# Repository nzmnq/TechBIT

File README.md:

# TechBIT Hardware (`scheme`) — Плата колісного вузла

Апаратна частина системи моніторингу вібрації, стану гальм/підшипників та температури коліс автомобіля **TechBIT**.  
Ця гілка (`scheme`) містить **лише апаратну частину (KiCad 10 PCB, 3D-моделі, генератори та файли для виготовлення)** — веб-додаток знаходиться у гілках `main` / `web-development`.

| Вигляд зверху (`F.Cu` — модулі та THT) | Вигляд знизу (`B.Cu` — SMD на міді) |
|---|---|
|  |  |

---

## Структура репозиторію

```text
.
├── kicad/                                      # Проєкт KiCad 10
│   ├── Wheel_Sensor_Amplifier.kicad_pro        # Файл проєкту KiCad 10
│   ├── Wheel_Sensor_Amplifier.kicad_sch        # Принципова схема та перелік зв'язків
│   ├── Wheel_Sensor_Amplifier.kicad_pcb        # Розводка плати (66 × 50 мм, 1 шар B.Cu)
│   └── Wheel_Sensor_Amplifier_Panel_A4.kicad_pcb  # Панель 3×5 (15 плат на аркуш A4)
├── 3dmodels/                                   # Локальні 3D-моделі модулів (.wrl)
├── renders/                                    # 3D-рендери та читабельна схема розмітки (.png)
├── print/                                      # Готові PDF 1:1 для ЛУТ, УФ-маски та монтажу
├── scripts/                                    # Python-скрипти генерації проєкту і макетів
│   ├── generate_project.py                     # Генератор KiCad-проєкту (single + 15x panel)
│   ├── make_plate_151x102.py                   # Генератор листів під текстоліт 151×102 мм
│   ├── make_a4_mixed_sheet.py                  # Генератор змішаного аркуша A4 (5 комплектів)
│   └── make_top_half_stencils.py               # Генератор УФ-маски на верхню половину A4
├── .gitignore
├── LICENSE
└── README.md
```

---

## Технічні характеристики плати (`Wheel Sensor Amplifier`)

- **Габарити однієї плати:** `66.0 × 50.0 мм` (оптимально для розміщення `2×2 = 4` плат на заготовці `151×102 мм` або `3×5 = 15` плат на A4).
- **Топологія:** **одностороння мідь (`B.Cu`)**, розведена без перемичок та без масивної заливки `GND` — розрахована під домашнє травлення (ЛУТ + лимонна кислота / перекис водню або хлорне залізо).
- **Гідроізоляція під заливку компаундом:** усі силові, шинні та сенсорні інтерфейси (`J1`, `J2`, `J3`) винесені кутовими роз'ємами по периметру для зручного заливання плати епоксидною смолою.
- **Паяльна маска:** розширення вікон `pad_to_mask_clearance = 0.15 мм`, суцільне заповнення контактних площадок на фотошаблонах (`B.Mask`).

---

## Склад компонентів (BOM)

### Верхня сторона (`F.Cu` — вивідні компоненти, модулі та роз'єми)
| Позиція | Компонент / Модуль | Номінал / Тип | Призначення |
|---|---|---|---|
| `U2` | Мікроконтролер | `ESP32-C3 SuperMini` | Оцифровка АЦП, I2C, CAN/TWAI (`USB-C` донизу) |
| `U1` | Операційний підсилювач | `MCP6002-I/P` (панелька `DIP-8`) | Зарядовий підсилювач ($K \approx 3$) + буфер |
| `MOD1` | DC-DC понижувач | `Mini360` (`12V → 5V`) | Живлення вузла від бортмережі авто |
| `MOD2` | CAN-трансивер | `SN65HVD230` (3.3V, 6-pin) | Інтерфейс CAN-шини (`CANH` / `CANL`) |
| `J1` | Клемник датчика вібрації | `15EDGR-5.08-02P` / `KF301-2P` (кутовий) | Вхід п'єзодатчика (`1=PIEZO+`, `2=GND`) |
| `J2` | Клемник живлення та CAN | `15EDGR-5.08-04P` / `KF301-4P` (кутовий) | Автомагістраль (`1=+12V`, `2=GND`, `3=CAN_L`, `4=CAN_H`) |
| `J3` | Роз'єм датчика температури | `JST-XH S4B-XH-A` (4-pin, кутовий 2.5 мм) | Вологостійкий датчик `GY-SHT40` (`1=3V3`, `2=GND`, `3=SDA`, `4=SCL`) |
| `R1` | Резистор THT 0.25W | `10 kΩ` | Обмеження вхідного струму ОП |
| `R2`, `R3` | Резистори THT 0.25W | `100 kΩ` (2 шт.) | Дільник опорної напруги `1.65 В` (`Vref`) |
| `R5` | Резистор THT 0.25W | `100 Ω` | Ізолюючий резистор перед ФНЧ та АЦП |
| `C5` | Конденсатор електролітичний | `10 µF` (радиальний D5/P2.5) | Фільтрація `Vref` (`+` до `VREF_1V65`) |

### Нижня сторона (`B.Cu` — SMD-монтаж на мідні доріжки)
| Позиція | Корпус | Номінал | Призначення |
|---|---|---|---|
| `D1` | `SOT-23` | `BAT54S` | Здвоєний діод Шотткі (захист входу від сплесків) |
| `C1` | `0805` | `1 nF` (NP0/C0G) | Вхідний розділовий конденсатор |
| `C2` | `0805` | `330 pF` (NP0/C0G, 50V) | Конденсатор зворотного зв'язку ($K = C_1/C_2 \approx 3$) |
| `R4` | `1206` | `4.7 MΩ` | Розрядний резистор зарядового інтегратора |
| `C3` | `1206` | `100 nF` | Блокування живлення `+3V3` біля `U1` |
| `C4` | `1206` | `100 nF` | ФНЧ антиаліасингу на вході АЦП (`R5 + C4`) |

---

## Розпіновка `ESP32-C3 SuperMini` (`U2`)

| Пін модуля | Сигнал (Net) | Підключення |
|---|---|---|
| Pin 16 (`5V`) | `+5V_BUCK` | Вихід `MOD1` (`Mini360`) |
| Pin 15 (`GND`) | `GND` | Загальна земля |
| Pin 14 (`3V3`) | `+3V3` | Живлення `U1`, `MOD2`, `J3`, `R2`, `D1` |
| Pin 11 | `ADC_SIGNAL` | Аналоговий вихід каскаду (`R5` / `C4`) |
| Pin 8 | `CAN_TX` | `MOD2` pin 3 |
| Pin 7 | `CAN_RX` | `MOD2` pin 4 |
| Pin 5 | `I2C_SCL` | `J3` pin 4 (`GY-SHT40 SCL`) |
| Pin 4 | `I2C_SDA` | `J3` pin 3 (`GY-SHT40 SDA`) |

---

## Свердління отворів

| Діаметр свердла | К-сть отворів (на 1 плату) | Елементи |
|---|---|---|
| **0.8 мм** | 40 | `R1, R2, R3, R5`, `C5`, панелька `U1` (`DIP-8`), гребінки `U2` і `MOD2` |
| **0.9 мм** | 4 | Боковий роз'єм `J3` (`JST-XH`) |
| **1.0 мм** | 4 | Контактні штирі `MOD1` (`Mini360`) |
| **1.3 мм** | 6 | Силові/шинні клемники `J1` і `J2` (`15EDGR-5.08` / `KF301`) |

---

## Файли для друку та виготовлення ([`print/`](print/))

> [!IMPORTANT]
> Друкуйте всі PDF **строго в масштабі `100%` / «Фактичний розмір»** (`Actual Size`). Вимикайте *Fit to Page* та *Borderless* (інакше драйвер розтягне плату на 2–3% і отвори не зійдуться). Перед перенесенням перевірте контрольні лінійки на аркуші (`150 мм` / `100 мм`).

| Файл | Призначення |
|---|---|
| `Plate_151x102_PagePro1350W_A4.pdf` | Оптимізовано під заготовку **`151×102 мм`** (4 плати `2×2`) та поля `≥ 4 мм`: мідь, дзеркальний верх, нижнє SMD-маркування, комбо-аркуш та УФ-маска |
| `SolderMask_UV_Film_Plate_151x102_A4.pdf` | Фотошаблони УФ паяльної маски під пластину `151×102 мм` (тонером вниз до міді + дзеркальний варіант) |
| `SolderMask_UV_Top_Half_A4.pdf` | УФ-маска, розміщена **тільки на верхній половині A4** (економія плівки: 2 плати, 4 плати `2×2`, або 2 пластини) |
| `A4_Mixed_Top_Bottom_Copper_5sets.pdf` | Змішаний аркуш A4: 5 повних комплектів (верх + мідь + низ SMD) + аркуш маркування |
| `Assembly_Guide_Readable_A4.pdf` | Читабельна карта монтажу та пайки (3 сторінки) |
| `LUT_Bottom_Copper_Max_Panel_15x_A4.pdf` / `_Single_A4.pdf` | Мідні доріжки `B.Cu` для ЛУТ (панель 15× або 1 плата) |
| `LUT_Top_Silkscreen_Transfer_Mirrored_15x_A4.pdf` / `_Single_A4.pdf` | Віддзеркалена верхня розмітка `F.SilkS` для переносу праскою |
| `LUT_Bottom_SMD_Markings_Single_A4.pdf` | Маркування SMD знизу (`B.SilkS`) |
| `SolderMask_UV_Film_15x_A4.pdf` / `_Single_A4.pdf` | Фотошаблони УФ-маски на панель 15× або 1 плату |

---

## Перегенерація та калібрування під принтер

Для повторної генерації файлів потрібні **Python 3**, **KiCad 10 (`kicad-cli`)**, **Google Chrome** (headless PDF) та `pypdf`:

```bash
# З кореня репозиторію:

# 1. Перегенерувати проєкт KiCad (одиночна плата, 15x панель, схема)
python3 scripts/generate_project.py

# 2. Перегенерувати аркуші для друку A4
python3 scripts/make_a4_mixed_sheet.py
python3 scripts/make_top_half_stencils.py

# 3. Перегенерувати аркуші під пластину 151x102 мм (з поправкою масштабу принтера у %)
python3 scripts/make_plate_151x102.py --sx 100.0 --sy 100.0
python3 scripts/make_plate_151x102.py --mask --sx 100.0 --sy 100.0
```

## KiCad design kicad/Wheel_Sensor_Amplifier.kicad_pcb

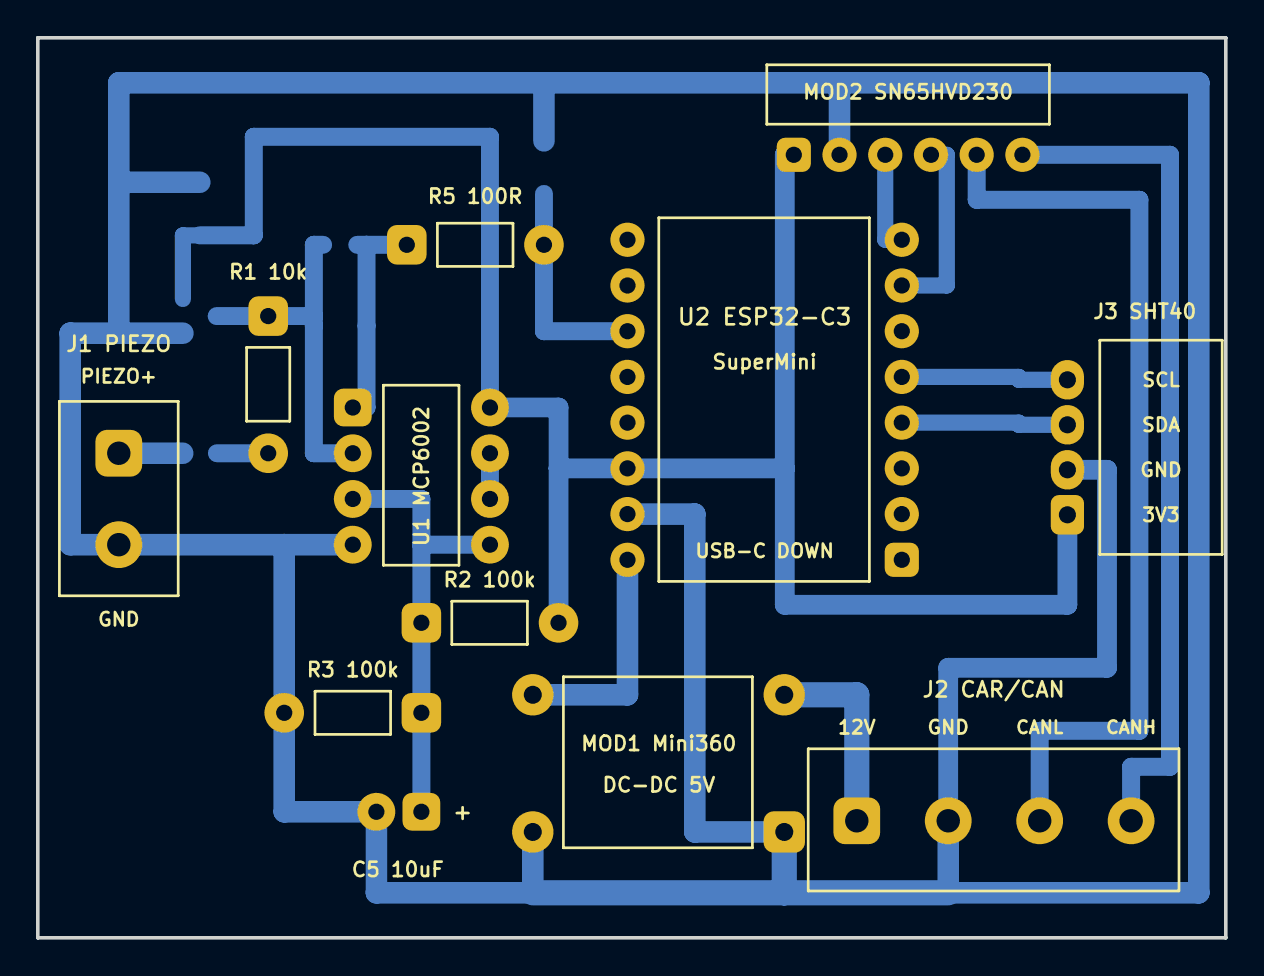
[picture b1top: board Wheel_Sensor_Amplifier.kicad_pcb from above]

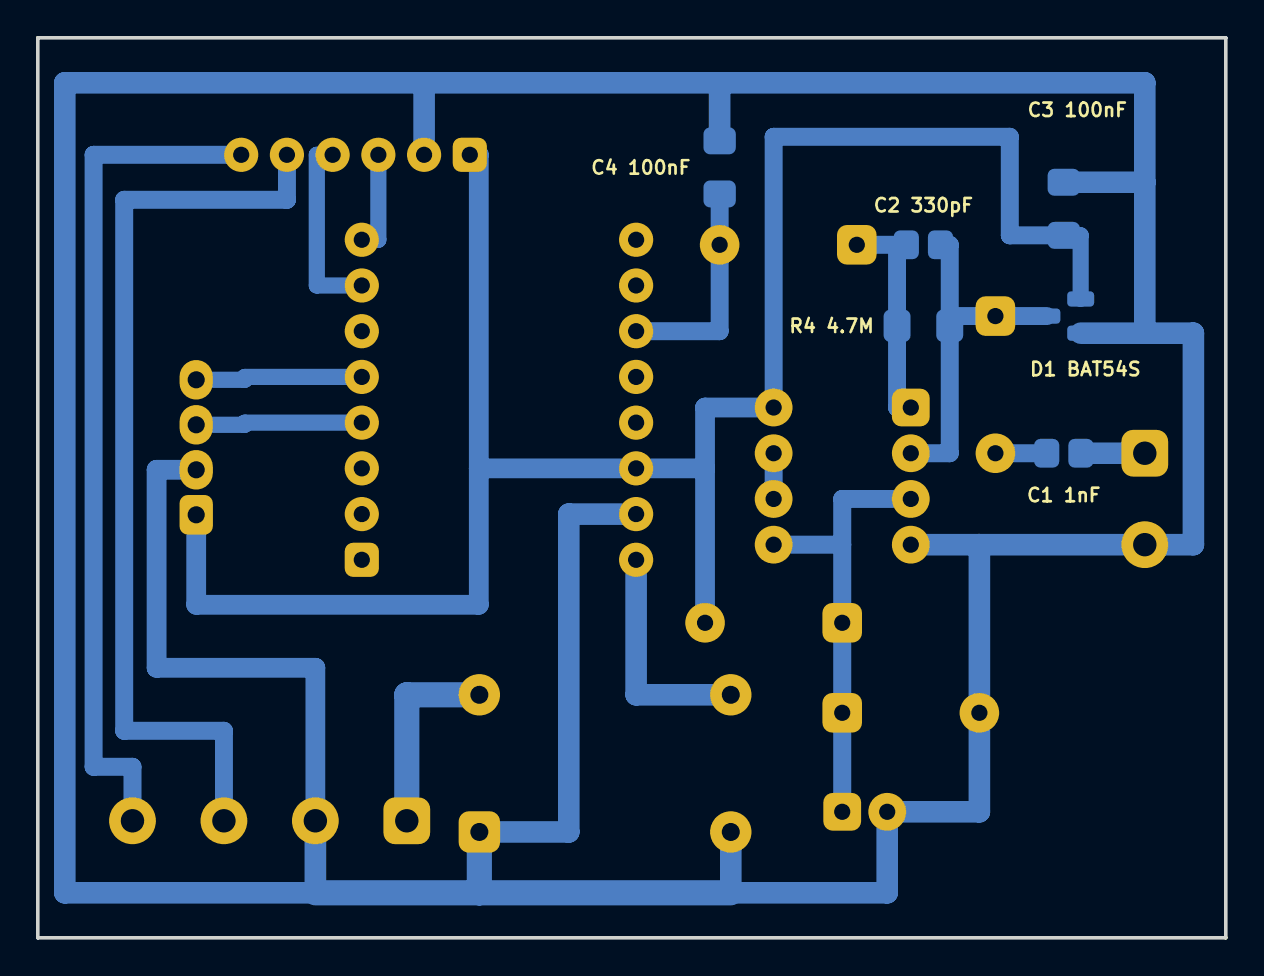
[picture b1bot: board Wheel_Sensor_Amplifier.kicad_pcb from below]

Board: 2 copper layers, 66.0 x 50.0 mm, 18 parts (6 on the bottom side), 17 nets.

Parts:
C1: 1nF; C_0805_2012Metric
C2: 330pF; C_0805_2012Metric
C3, C4: 100nF; C_1206_3216Metric
C5: 10uF; CP_Radial_D5.0mm_P2.50mm
D1: BAT54S; SOT-23
J1: PIEZO_IN; TerminalBlock_Phoenix_MKDS-1,5-2-5.08_1x02_P5.08mm_Horizont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
J2: 12V_GND_CAN; TerminalBlock_Phoenix_MKDS-1,5-4-5.08_1x04_P5.08mm_Horizont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
J3: GY-SHT40_SIDE; JST_XH_S4B-XH-A_1x04_P2.50mm_Horizontal
MOD1: Mini360_5V; Mini360_Buck
MOD2: SN65HVD230_CAN; PinHeader_1x06_P2.54mm_Vertical
R1: 10k; R_Axial_DIN0207_L6.3mm_D2.5mm_P7.62mm_Horizontal
R2, R3: 100k; R_Axial_DIN0207_L6.3mm_D2.5mm_P7.62mm_Horizontal
R4: 4.7M; R_1206_3216Metric
R5: 100R; R_Axial_DIN0207_L6.3mm_D2.5mm_P7.62mm_Horizontal
U1: MCP6002-I/P; DIP-8_W7.62mm_Socket
U2: ESP32-C3_SuperMini

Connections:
+3V3: C3.1, D1.2, J3.1, MOD2.1, R2.2, U1.8, U2.14
+5V_BUCK: MOD1.4, U2.16
+12V_RAW: J2.1, MOD1.2
ADC_SIGNAL: C4.1, R5.2, U2.11
AMP_OUT1: C2.2, R4.2, R5.1, U1.1
CAN_H: J2.4, MOD2.6
CAN_L: J2.3, MOD2.5
CAN_RX: MOD2.4, U2.7
CAN_TX: MOD2.3, U2.8
GND: C3.2, C4.2, C5.2, D1.1, J1.2, J2.2, J3.2, MOD1.1, MOD1.3, MOD2.2, R3.2, U1.4, U2.15
I2C_SCL: J3.4, U2.5
I2C_SDA: J3.3, U2.4
NODE_C1_R1: C1.2, R1.2
PIEZO_IN: C1.1, J1.1
SUM_NODE: C2.1, D1.3, R1.1, R4.1, U1.2
U1B_OUT: U1.6, U1.7
VREF_1V65: C5.1, R2.1, R3.1, U1.3, U1.5
